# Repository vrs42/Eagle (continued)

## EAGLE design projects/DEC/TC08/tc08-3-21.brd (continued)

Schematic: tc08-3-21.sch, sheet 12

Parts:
A02, A03, A04, A05, A06: M903; H807
A13, A17, A27, A28: H807
A24: W023; H807
A25, A26: M916; H807
B17, B24, B25, B26, B27, B28: H807
C19, C20, C21, C22, C23, C24, C25, C26, C27, C28: H807
D01, D19, D20, D21, D22, D23, D24, D25, D26, D27, D28: H807
D02, D03, D04, D05, D06: M903; H807

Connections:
!DB_00: A06.B1, D06.B1; also elsewhere on the board
!DB_01: A06.D1, D06.D1; also elsewhere on the board
!DB_02: A06.E1, D06.E1; also elsewhere on the board
!DB_03: A06.H1, D06.H1; also elsewhere on the board
!DB_04: A06.J1, D06.J1; also elsewhere on the board
!DB_05: A06.L1, D06.L1; also elsewhere on the board
!DB_06: A06.M1, D06.M1; also elsewhere on the board
!DB_07: A06.P1, D06.P1; also elsewhere on the board
!DB_08: A06.S1, D06.S1; also elsewhere on the board
!DB_09: A06.D2, D06.D2; also elsewhere on the board
!DB_10: A06.E2, D06.E2; also elsewhere on the board
!DB_11: A06.H2, D06.H2; also elsewhere on the board
!EA_00: A06.V2, D06.V2; also elsewhere on the board
!EA_01: A06.T2, D06.T2; also elsewhere on the board
!EA_02: A06.S2, D06.S2; also elsewhere on the board
!IM_00: A04.B1, D04.B1; also elsewhere on the board
!IM_01: A04.D1, D04.D1; also elsewhere on the board
!IM_02: A04.E1, D04.E1; also elsewhere on the board
!IM_03: A04.H1, D04.H1; also elsewhere on the board
!IM_04: A04.J1, D04.J1; also elsewhere on the board
!IM_05: A04.L1, D04.L1; also elsewhere on the board
!IM_06: A04.M1, D04.M1; also elsewhere on the board
!IM_07: A04.P1, D04.P1; also elsewhere on the board
!IM_08: A04.S1, D04.S1; also elsewhere on the board
!IM_09: A04.D2, D04.D2; also elsewhere on the board
!IM_10: A04.E2, D04.E2
!IM_11: A04.H2, D04.H2; also elsewhere on the board
!T_00: A24.V2; also elsewhere on the board
!T_01: A24.M2; also elsewhere on the board
!T_02: A24.N2; also elsewhere on the board
!T_03: A24.P2; also elsewhere on the board
!T_04: A24.R2; also elsewhere on the board
!T_05: A24.S2; also elsewhere on the board
!T_06: A24.T2; also elsewhere on the board
!T_07: A24.U2; also elsewhere on the board
!T_FWD: A24.E2; also elsewhere on the board
!T_GO: A24.C2; also elsewhere on the board
!T_PWR_CLR: A24.H2; also elsewhere on the board
!T_REV: A24.F2; also elsewhere on the board
!T_SINGLE_UNIT: A24.K2; also elsewhere on the board
!T_STOP: A24.D2; also elsewhere on the board
!T_WRITE_OK: A24.L2; also elsewhere on the board
C00: A26.E2; also elsewhere on the board
C01: A26.F2; also elsewhere on the board
DATA: A26.M1; also elsewhere on the board
DF: A26.E1; also elsewhere on the board
DTB_00: A25.A2; also elsewhere on the board
DTB_01: A25.B2; also elsewhere on the board
DTB_02: A25.C2; also elsewhere on the board
DTB_03: A25.D2; also elsewhere on the board
DTB_04: A25.E2; also elsewhere on the board
DTB_05: A25.F2; also elsewhere on the board
DTB_06: A25.H2; also elsewhere on the board
DTB_07: A25.J2; also elsewhere on the board
DTB_08: A25.K2; also elsewhere on the board
DTB_09: A25.L2; also elsewhere on the board
DTB_10: A25.M2; also elsewhere on the board
DTB_11: A25.N2; also elsewhere on the board
DTF: A26.C1; also elsewhere on the board
EF: A25.N1; also elsewhere on the board
END: A25.R1; also elsewhere on the board
ENI: A25.L1; also elsewhere on the board
FR_00: A25.F1; also elsewhere on the board
FR_01: A25.H1; also elsewhere on the board
FR_02: A25.J1; also elsewhere on the board
FR_03: A25.K1; also elsewhere on the board
GND: A02.A1 (GND), A02.C1 (GND), A02.C2 (GND), A02.F1 (GND), A02.F2 (GND), A02.J2 (GND), A02.K1 (GND), A02.L2 (GND), A02.N1 (GND), A02.N2 (GND), A02.R1 (GND), A02.R2 (GND), A02.T1 (GND), A02.U2 (GND), A03.A1 (GND), A03.C1 (GND), A03.C2 (GND), A03.F1 (GND), A03.F2 (GND), A03.J2 (GND), A03.K1 (GND), A03.L2 (GND), A03.N1 (GND), A03.N2 (GND), A03.R1 (GND), A03.R2 (GND), A03.T1 (GND), A03.U2 (GND), A04.A1 (GND), A04.C1 (GND), A04.C2 (GND), A04.F1 (GND), A04.F2 (GND), A04.J2 (GND), A04.K1 (GND), A04.L2 (GND), A04.N1 (GND), A04.N2 (GND), A04.R1 (GND), A04.R2 (GND), A04.T1 (GND), A04.U2 (GND), A05.A1 (GND), A05.B1, A05.C1 (GND), A05.C2 (GND), A05.D1, A05.D2, A05.E1, A05.F1 (GND), A05.F2 (GND), A05.H1, A05.J1, A05.J2 (GND), A05.K1 (GND), A05.L1, A05.L2 (GND), A05.M1, A05.N1 (GND), A05.N2 (GND), A05.P1, A05.R1 (GND), A05.R2 (GND), A05.S1, A05.T1 (GND), A05.U2 (GND), A06.A1 (GND), A06.C1 (GND), A06.C2 (GND), A06.F1 (GND), A06.F2 (GND), A06.J2 (GND), A06.K1 (GND), A06.K2, A06.L2 (GND), A06.N1 (GND), A06.N2 (GND), A06.R1 (GND), A06.R2 (GND), A06.T1 (GND), A06.U2 (GND), A25.M1, A26.D2, A26.U2, A26.V1, D02.A1 (GND), D02.C1 (GND), D02.C2 (GND), D02.F1 (GND), D02.F2 (GND), D02.J2 (GND), D02.K1 (GND), D02.L2 (GND), D02.N1 (GND), D02.N2 (GND), D02.R1 (GND), D02.R2 (GND), D02.T1 (GND), D02.U2 (GND), D03.A1 (GND), D03.C1 (GND), D03.C2 (GND), D03.F1 (GND), D03.F2 (GND), D03.J2 (GND), D03.K1 (GND), D03.L2 (GND), D03.N1 (GND), D03.N2 (GND), D03.R1 (GND), D03.R2 (GND), D03.T1 (GND), D03.U2 (GND), D04.A1 (GND), D04.C1 (GND), D04.C2 (GND), D04.F1 (GND), D04.F2 (GND), D04.J2 (GND), D04.K1 (GND), D04.L2 (GND), D04.N1 (GND), D04.N2 (GND), D04.R1 (GND), D04.R2 (GND), D04.T1 (GND), D04.U2 (GND), D05.A1 (GND), D05.B1, D05.C1 (GND), D05.C2 (GND), D05.D1, D05.D2, D05.E1, D05.F1 (GND), D05.F2 (GND), D05.H1, D05.J1, D05.J2 (GND), D05.K1 (GND), D05.L1, D05.L2 (GND), D05.M1, D05.N1 (GND), D05.N2 (GND), D05.P1, D05.R1 (GND), D05.R2 (GND), D05.S1, D05.T1 (GND), D05.U2 (GND), D06.A1 (GND), D06.C1 (GND), D06.C2 (GND), D06.F1 (GND), D06.F2 (GND), D06.J2 (GND), D06.K1 (GND), D06.K2, D06.L2 (GND), D06.N1 (GND), D06.N2 (GND), D06.R1 (GND), D06.R2 (GND), D06.T1 (GND), D06.U2 (GND); also elsewhere on the board
I/!O_0_TO_AC: A04.P2, D04.P2; also elsewhere on the board
I/!O_1_TO_CA_INH: A06.M2, D06.M2; also elsewhere on the board
I/!O_ADDR_ACC: A05.S2, D05.S2; also elsewhere on the board
I/!O_BMB_03: A03.H1, D03.H1
I/!O_BMB_04: A03.L1, D03.L1
I/!O_BMB_05: A03.P1, D03.P1
I/!O_BMB_06: A03.D2, D03.D2
I/!O_BMB_07: A03.H2, D03.H2
I/!O_BMB_08: A03.M2, D03.M2; also elsewhere on the board
I/!O_BRK_RQ: A05.K2, D05.K2; also elsewhere on the board
I/!O_BWC0: A06.P2, D06.P2; also elsewhere on the board
I/!O_INT_RQ: A04.M2, D04.M2; also elsewhere on the board
I/!O_SKP_RQ: A04.K2, D04.K2; also elsewhere on the board
I/O_B-BRK: A05.P2, D05.P2; also elsewhere on the board
I/O_B-RUN: A04.S2, D04.S2; also elsewhere on the board
I/O_BAC_00: A02.B1, D02.B1; also elsewhere on the board
I/O_BAC_01: A02.D1, D02.D1; also elsewhere on the board
I/O_BAC_02: A02.E1, D02.E1; also elsewhere on the board
I/O_BAC_03: A02.H1, D02.H1; also elsewhere on the board
I/O_BAC_04: A02.J1, D02.J1; also elsewhere on the board
I/O_BAC_05: A02.L1, D02.L1; also elsewhere on the board
I/O_BAC_06: A02.M1, D02.M1; also elsewhere on the board
I/O_BAC_07: A02.P1, D02.P1; also elsewhere on the board
I/O_BAC_08: A02.S1, D02.S1; also elsewhere on the board
I/O_BAC_09: A02.D2, D02.D2; also elsewhere on the board
I/O_BAC_10: A02.E2, D02.E2; also elsewhere on the board
I/O_BAC_11: A02.H2, D02.H2; also elsewhere on the board
I/O_BMB_00: A03.B1, D03.B1; also elsewhere on the board
I/O_BMB_01: A03.D1, D03.D1; also elsewhere on the board
I/O_BMB_02: A03.E1, D03.E1; also elsewhere on the board
I/O_BMB_03: A03.J1, D03.J1; also elsewhere on the board
I/O_BMB_04: A03.M1, D03.M1; also elsewhere on the board
I/O_BMB_05: A03.S1, D03.S1; also elsewhere on the board
I/O_BMB_06: A03.E2, D03.E2; also elsewhere on the board
I/O_BMB_07: A03.K2, D03.K2; also elsewhere on the board
I/O_BMB_08: A03.P2, D03.P2; also elsewhere on the board
I/O_BMB_09: A03.S2, D03.S2; also elsewhere on the board
I/O_BMB_10: A03.T2, D03.T2; also elsewhere on the board
I/O_BMB_11: A03.V2, D03.V2; also elsewhere on the board
I/O_DATA_IN: A05.M2, D05.M2; also elsewhere on the board
I/O_PWR_CLR: A02.V2, D02.V2; also elsewhere on the board
I/O_TS03: A02.S2, D02.S2; also elsewhere on the board
I/O_TS04: A02.T2, D02.T2
IOP_1: A02.K2, D02.K2; also elsewhere on the board
IOP_2: A02.M2, D02.M2; also elsewhere on the board
IOP_4: A02.P2, D02.P2; also elsewhere on the board
LPB_00: A25.T2; also elsewhere on the board
LPB_01: A25.U2; also elsewhere on the board
LPB_02: A25.V2; also elsewhere on the board
LPB_03: A26.A2; also elsewhere on the board
LPB_04: A26.B2; also elsewhere on the board
LPB_05: A26.C2; also elsewhere on the board
MC00: A26.S1; also elsewhere on the board
MC01: A26.T1; also elsewhere on the board
MC02: A26.U1; also elsewhere on the board
MF00: A25.V1; also elsewhere on the board
MF01: A26.A1; also elsewhere on the board
MF02: A26.B1; also elsewhere on the board
MKT: A26.H2; also elsewhere on the board
MKTK: A25.P1; also elsewhere on the board
MR00: A25.D1; also elsewhere on the board
MR01: A25.E1; also elsewhere on the board
PAR: A25.T1; also elsewhere on the board
SEL: A25.S1; also elsewhere on the board
ST_BLK_MK: A26.K1; also elsewhere on the board
ST_CK: A26.P1; also elsewhere on the board
ST_FINAL: A26.N1; also elsewhere on the board
ST_IDLE: A26.R1; also elsewhere on the board
ST_REV_CK: A26.L1; also elsewhere on the board
SWTM: A26.V2; also elsewhere on the board
TIM: A25.U1; also elsewhere on the board
USR_00: A25.A1; also elsewhere on the board
USR_01: A25.B1; also elsewhere on the board
USR_02: A25.C1; also elsewhere on the board
UTS: A26.J1; also elsewhere on the board
W01: A26.J2; also elsewhere on the board
W02: A26.K2; also elsewhere on the board
W03: A26.L2; also elsewhere on the board
W04: A26.M2; also elsewhere on the board
W05: A26.N2; also elsewhere on the board
W06: A26.P2; also elsewhere on the board
W07: A26.R2; also elsewhere on the board
W08: A26.S2; also elsewhere on the board
W09: A26.T2; also elsewhere on the board
WB00: A25.P2; also elsewhere on the board
WB01: A25.R2; also elsewhere on the board
WB02: A25.S2; also elsewhere on the board
WC: A26.H1; also elsewhere on the board
WR_EN: A26.F1; also elsewhere on the board

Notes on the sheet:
Empty Slots:

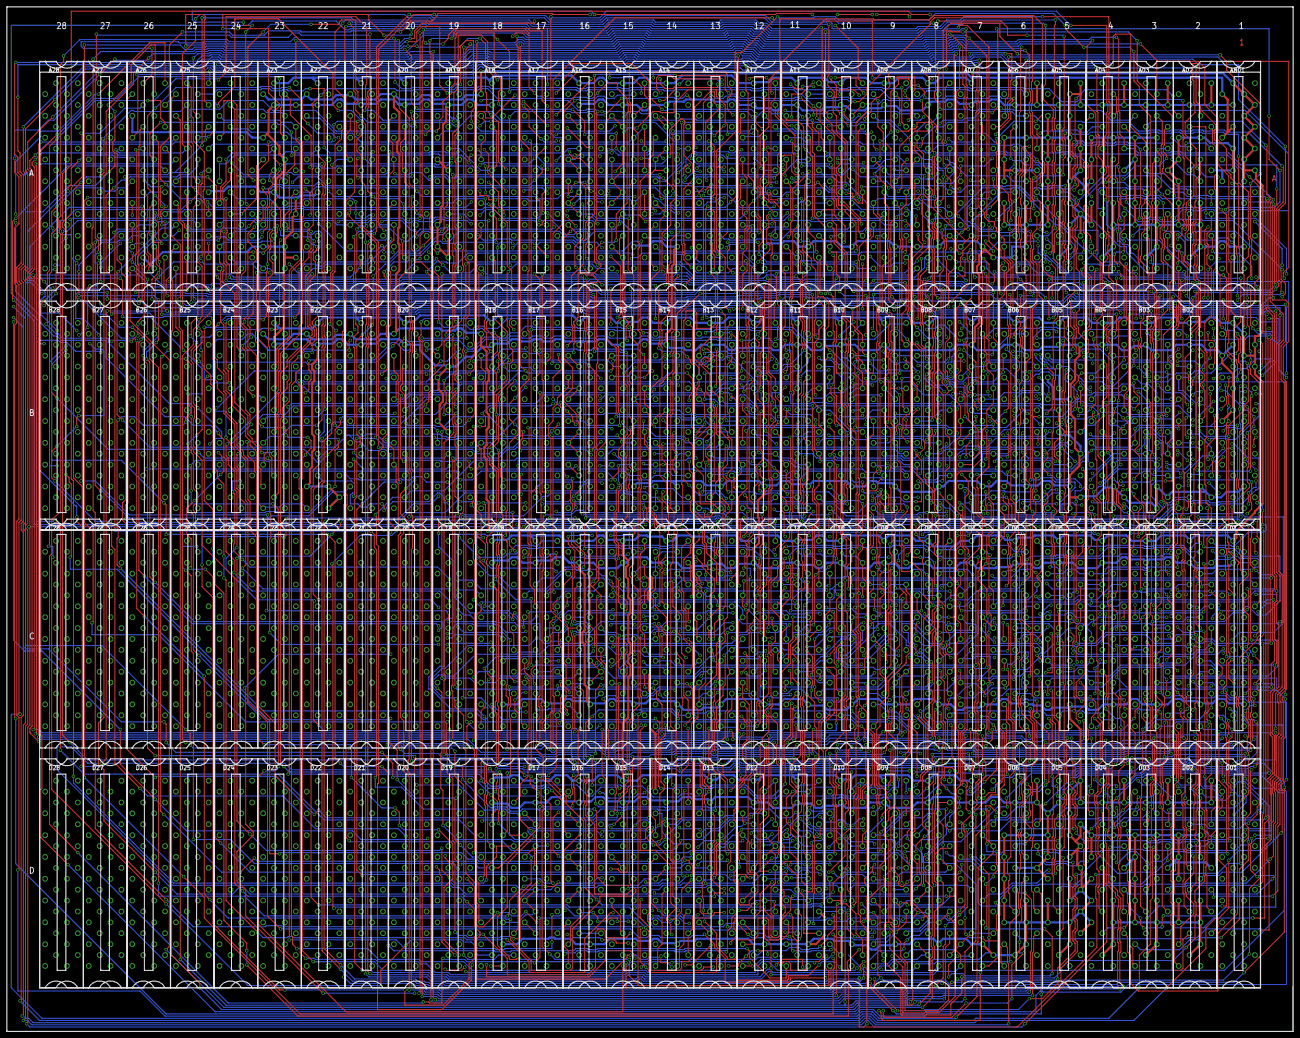
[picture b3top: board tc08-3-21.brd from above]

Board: 4 copper layers, 374.7 x 298.4 mm, 123 parts (0 on the bottom side), 535 nets.

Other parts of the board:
U$17, U$18, U$19, U$20, U$66, U$67, U$68, U$69, U$70, U$71, U$72, U$73, U$74, U$75: CBLOCK

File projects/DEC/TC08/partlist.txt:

Partlist

Exported from tc08.sch at  8/08/2006 10:36:56a

EAGLE Version 4.11 Copyright (c) 1988-2003 CadSoft

Part     Value          Device     Package  Library  Sheet

A02      M903           M903       H807     dec-m    12
A03      M903           M903       H807     dec-m    12
A04      M903           M903       H807     dec-m    12
A05      M903           M903       H807     dec-m    12
A06      M903           M903       H807     dec-m    12
A07      M161           M161       H807     dec-m    2
A08      M206           M206X      H807     dec-m    4
A09      M117           M117       H807     dec-m    2
A10      M113           M113       H807     dec-m    2
A11      M111           M111       H807     dec-m    1
A12      M113           M113       H807     dec-m    1
A14      M302           M302       H807     dec-m    3
A15      M627           M627       H807     dec-m    3
A16      M602           M602       H807     dec-m    3
A18      G888           G888       H807     dec-m    10
A20      G888           G888       H807     dec-m    10
A21      G888           G888       H807     dec-m    10
A22      M502           M502       H807     dec-m    2
A23      M633           M633       H807     dec-m    2
A24      W023           W023       H807     dec-m    12
A25      M916           M916       H807     dec-m    12
A26      M916           M916       H807     dec-m    12
AB01     G821           G821       H807-2   dec-m    10
AB19     W032           W032       H807-2   dec-m    10
B02      M623           M623       H807     dec-m    11
B03      M623           M623       H807     dec-m    11
B04      M623           M623       H807     dec-m    11
B05      M623           M623       H807     dec-m    11
B06      M111           M111       H807     dec-m    1
B07      M207           M207       H807     dec-m    2
B08      M113           M113       H807     dec-m    1
B09      M206           M206X      H807     dec-m    8
B10      M627           M627       H807     dec-m    1
B11      M115           M115       H807     dec-m    2
B12      M117           M117       H807     dec-m    4
B13      M206           M206X      H807     dec-m    4
B14      M206           M206X      H807     dec-m    2
B15      M113           M113       H807     dec-m    3
B16      M602           M602       H807     dec-m    3
B18      G888           G888       H807     dec-m    10
B20      G888           G888       H807     dec-m    10
B21      G879           G879       H807     dec-m    6
B22      M633           M633       H807     dec-m    2
B23      W005           W005       H807     dec-m    2
C01      M101           M101       H807     dec-m    1
C02      M101           M101-ARRAY H807     dec-m    11
C03      M101           M101-ARRAY H807     dec-m    11
C04      M103           M103       H807     dec-m    1
C05      M103           M103       H807     dec-m    1
C06      M111           M111       H807     dec-m    1
C07      M207           M207       H807     dec-m    2
C08      M121           M121       H807     dec-m    1
C09      M206           M206X      H807     dec-m    8
C10      M121           M121       H807     dec-m    6
C11      M113           M113       H807     dec-m    4
C12      M115           M115       H807     dec-m    3
C13      M111           M111       H807     dec-m    3
C14      M206           M206X      H807     dec-m    3
C15      M113           M113       H807     dec-m    3
C16      M627           M627       H807     dec-m    1
C17      M111           M111       H807     dec-m    1
CD18     M228           M228       H807-2   dec-m    7
D02      M903           M903       H807     dec-m    12
D03      M903           M903       H807     dec-m    12
D04      M903           M903       H807     dec-m    12
D05      M903           M903       H807     dec-m    12
D06      M903           M903       H807     dec-m    12
D07      M161           M161       H807     dec-m    2
D08      M207           M207       H807     dec-m    9
D09      M121           M121       H807     dec-m    2
D10      M119           M119       H807     dec-m    3
D11      M206           M206X      H807     dec-m    1
D12      M627           M627       H807     dec-m    1
D13      M602           M602       H807     dec-m    1
D14      M307           M307       H807     dec-m    3
D15      M401           M401       H807     dec-m    3
D16      M302           M302       H807     dec-m    6
D17      M602           M602       H807     dec-m    1
